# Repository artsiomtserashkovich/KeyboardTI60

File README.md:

TI60
===

A common 60% PCB with RGB Backlight.

## TI60 Hardware Information

    MCU: Atmega32u4
    Led Driver: IS31FL3731
    Leds: WS2812
    
    Led Pin: D2
    Led Drive Pins: D0 D1 (I2C) 

    /* Column pin configuration
    * col: 1   2   3   4   5   6   7   8   9   10   11  12  13  14  15
    * pin: F1  B0  F5  B1  F6  B2  F7  B3  C7  B7   C6  D3  B6  D5  F0
    */
     
    /* Row pin configuration
    * row: 1   2   3   4   5
    * pin: D4  D6  D7  B4  B5
    */

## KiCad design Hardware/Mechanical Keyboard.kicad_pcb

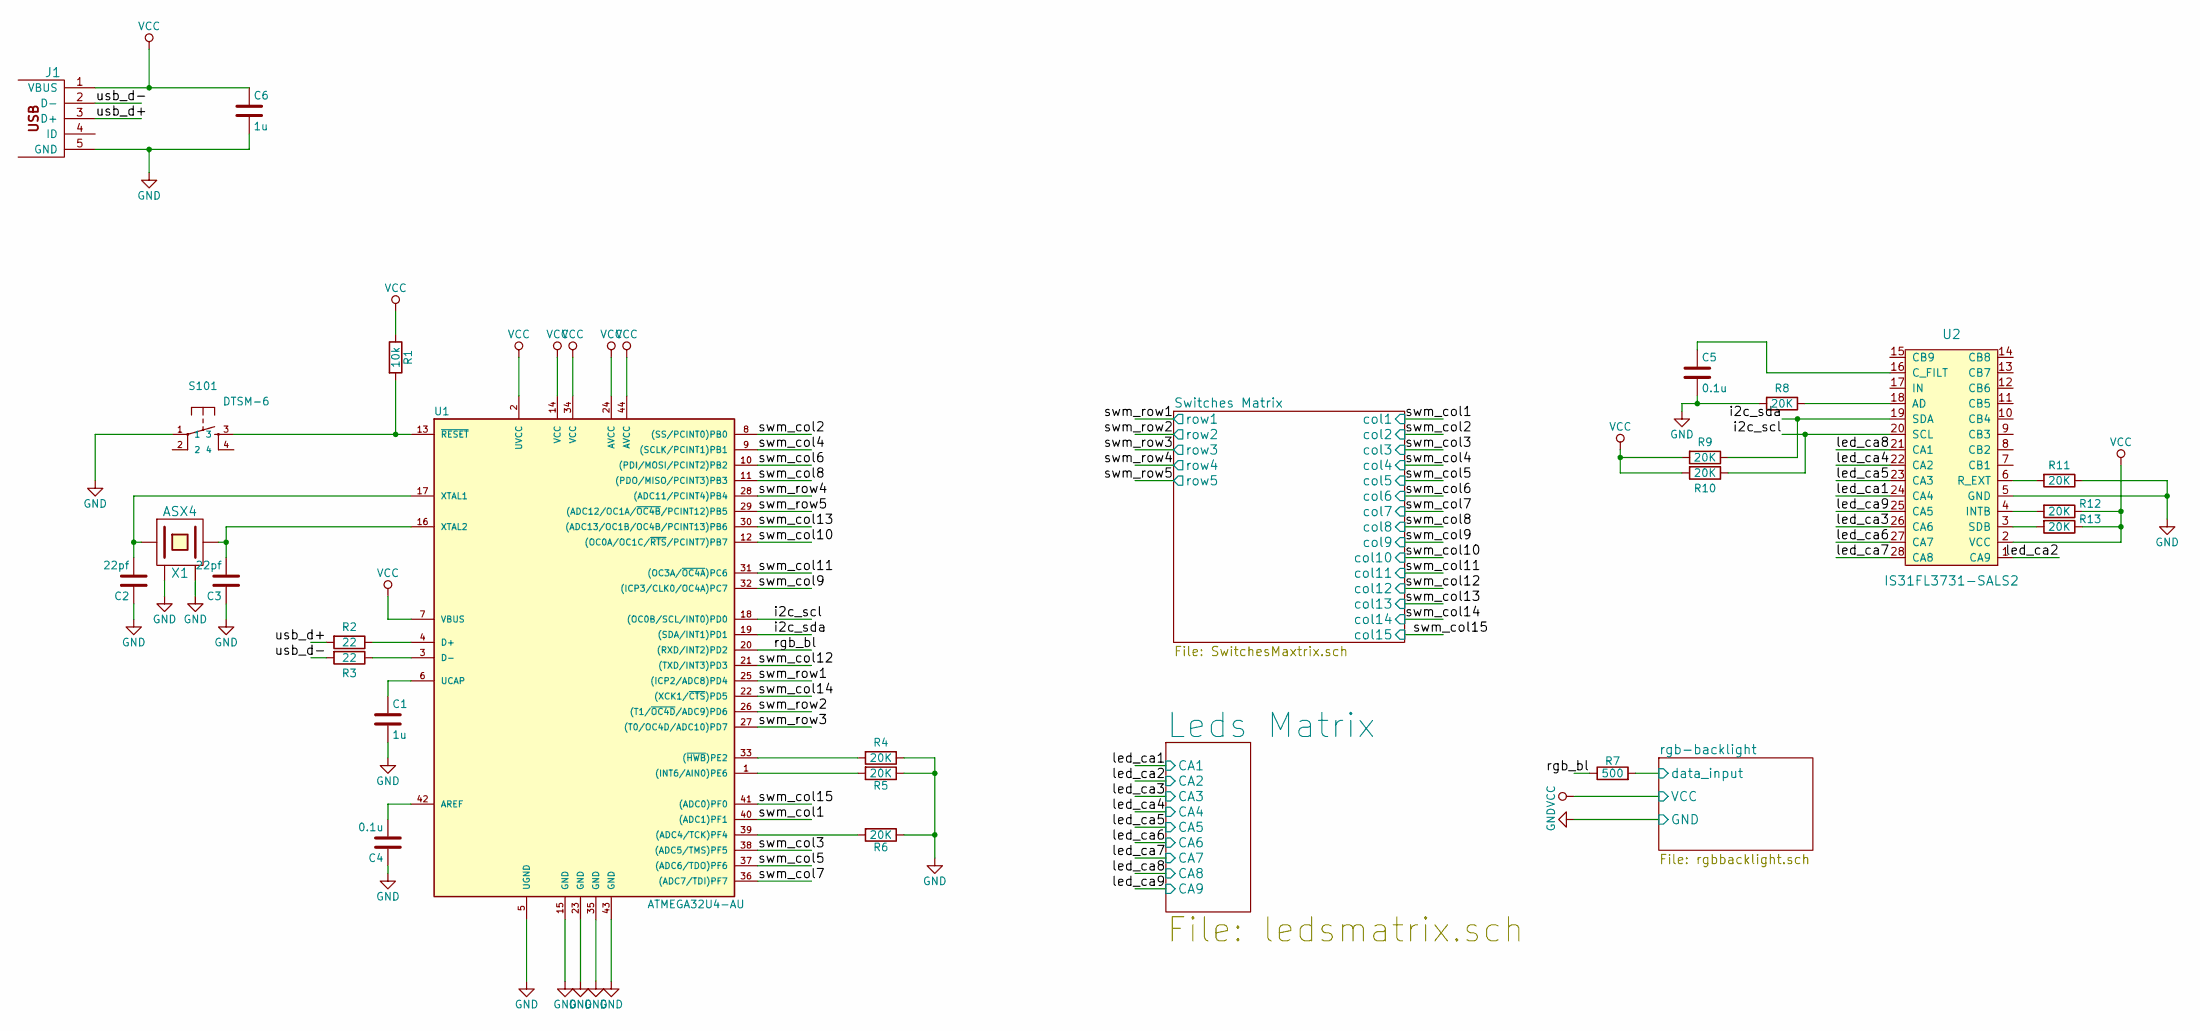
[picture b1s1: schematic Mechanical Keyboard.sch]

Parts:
C1, C6: 1u; C_0805_HandSoldering
C2, C3: 22pf; C_0805_HandSoldering
C4, C5: 0.1u; C_0805_HandSoldering
J1: USBMINI_B05; 67503
R1: 10k; R_0805_HandSoldering
R2, R3: 22; R_0805_HandSoldering
R4, R5, R6, R8, R9, R10, R11, R12, R13: 20K; R_0805_HandSoldering
R7: 500; R_0805_HandSoldering
S101: DTSM-6; KSEM31GLFS
U1: ATMEGA32U4-AU; TQFP-44_10x10mm_Pitch0.8mm
U2: IS31FL3731-SALS2; QFN-28-1EP_4x4mm_Pitch0.4mm
X1: ASX4; 4-SMD

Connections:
/i2c_scl: R10.1, U1.18 ((OC0B/SCL/INT0)PD0), U2.20 (SCL)
/i2c_sda: R9.1, U1.19 ((SDA/INT1)PD1), U2.19 (SDA)
/led_ca1: U2.24 (CA4); also elsewhere on the board
/led_ca2: U2.1 (CA9); also elsewhere on the board
/led_ca3: U2.26 (CA6); also elsewhere on the board
/led_ca4: U2.22 (CA2); also elsewhere on the board
/led_ca5: U2.23 (CA3); also elsewhere on the board
/led_ca6: U2.27 (CA7); also elsewhere on the board
/led_ca7: U2.28 (CA8); also elsewhere on the board
/led_ca8: U2.21 (CA1); also elsewhere on the board
/led_ca9: U2.25 (CA5); also elsewhere on the board
/rgb-backlight/data_input: R7.2; also elsewhere on the board
/rgb_bl: R7.1, U1.20 ((RXD/INT2)PD2)
/swm_col1: U1.40 ((ADC1)PF1); also elsewhere on the board
/swm_col2: U1.8 ((SS/PCINT0)PB0); also elsewhere on the board
/swm_col3: U1.38 ((ADC5/TMS)PF5); also elsewhere on the board
/swm_col4: U1.9 ((SCLK/PCINT1)PB1); also elsewhere on the board
/swm_col5: U1.37 ((ADC6/TDO)PF6); also elsewhere on the board
/swm_col6: U1.10 ((PDI/MOSI/PCINT2)PB2); also elsewhere on the board
/swm_col7: U1.36 ((ADC7/TDI)PF7); also elsewhere on the board
/swm_col8: U1.11 ((PDO/MISO/PCINT3)PB3); also elsewhere on the board
/swm_col9: U1.32 ((ICP3/CLK0/OC4A)PC7); also elsewhere on the board
/swm_col10: U1.12 ((OC0A/OC1C/~RTS~/PCINT7)PB7); also elsewhere on the board
/swm_col11: U1.31 ((OC3A/~OC4A~)PC6); also elsewhere on the board
/swm_col12: U1.21 ((TXD/INT3)PD3); also elsewhere on the board
/swm_col13: U1.30 ((ADC13/OC1B/OC4B/PCINT13)PB6); also elsewhere on the board
/swm_col14: U1.22 ((XCK1/~CTS~)PD5); also elsewhere on the board
/swm_col15: U1.41 ((ADC0)PF0); also elsewhere on the board
/swm_row1: U1.25 ((ICP2/ADC8)PD4); also elsewhere on the board
/swm_row2: U1.26 ((T1/~OC4D~/ADC9)PD6); also elsewhere on the board
/swm_row3: U1.27 ((T0/OC4D/ADC10)PD7); also elsewhere on the board
/swm_row4: U1.28 ((ADC11/PCINT4)PB4); also elsewhere on the board
/swm_row5: U1.29 ((ADC12/OC1A/~OC4B~/PCINT12)PB5); also elsewhere on the board
/usb_d+: J1.3 (D+), R2.2
/usb_d-: J1.2 (D-), R3.2
GND: C1.2, C2.1, C3.1, C4.1, C5.2, C6.2, J1.5 (GND), R4.1, R5.1, R6.1, R8.2, R11.1, S101.1, U1.5 (UGND), U1.15 (GND), U1.23 (GND), U1.35 (GND), U1.43 (GND), U2.5 (GND), X1.2 (GND), X1.4 (GND); also elsewhere on the board
unnamed: C1.1, U1.6 (UCAP)
unnamed: C2.2, U1.17 (XTAL1), X1.1
unnamed: C3.2, U1.16 (XTAL2), X1.3 (2)
unnamed: C4.2, U1.42 (AREF)
unnamed: C5.1, U2.16 (C_FILT)
unnamed: R1.2, S101.3, U1.13 (~RESET~)
unnamed: R2.1, U1.4 (D+)
unnamed: R3.1, U1.3 (D-)
unnamed: R4.2, U1.33 ((~HWB~)PE2)
unnamed: R5.2, U1.1 ((INT6/AIN0)PE6)
unnamed: R6.2, U1.39 ((ADC4/TCK)PF4)
unnamed: R8.1, U2.18 (AD)
unnamed: R11.2, U2.6 (R_EXT)
unnamed: R12.2, U2.4 (INTB)
unnamed: R13.2, U2.3 (SDB)
VCC: C6.1, J1.1 (VBUS), R1.1, R9.2, R10.2, R12.1, R13.1, U1.2 (UVCC), U1.7 (VBUS), U1.14 (VCC), U1.24 (AVCC), U1.34 (VCC), U1.44 (AVCC), U2.2 (VCC); also elsewhere on the board

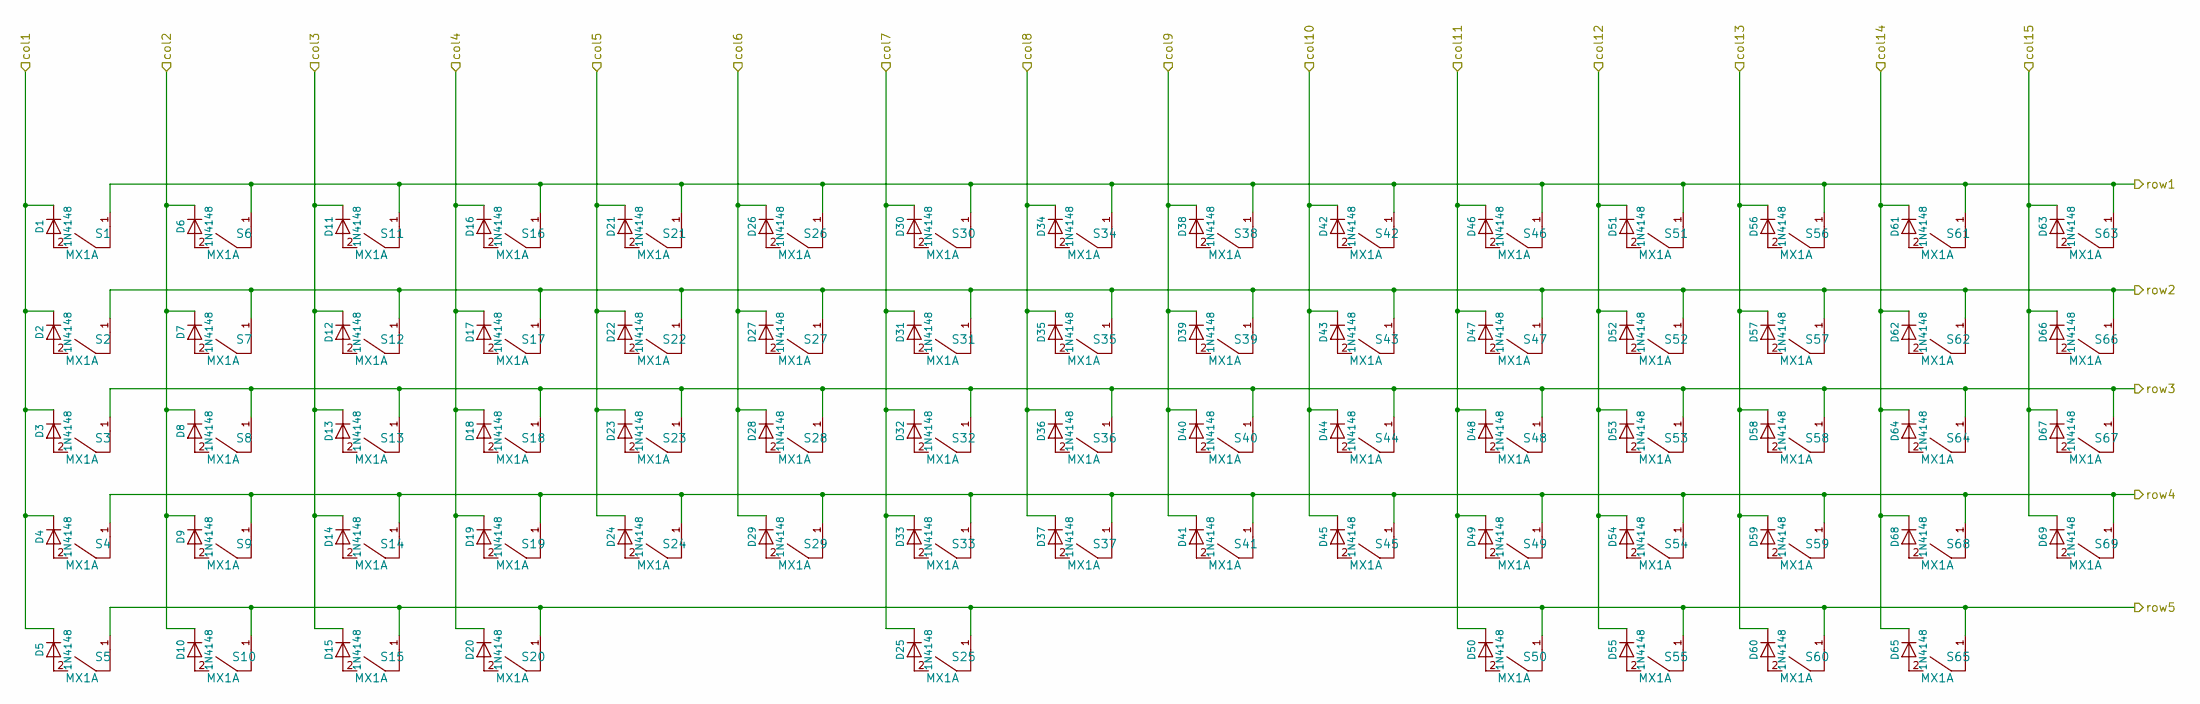
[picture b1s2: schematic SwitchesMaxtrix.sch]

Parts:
D1, D2, D3, D4, D5, D6, D7, D8, D9, D10, D11, D12, D13, D14, D15, D16, D17, D18, D19, D20, D21, D22, D23, D24, D25, D26, D27, D28, D29, D30, D31, D32, D33, D34, D35, D36, D37, D38, D39, D40, D41, D42, D43, D44, D45, D46, D47, D48, D49, D50, D51, D52, D53, D54, D55, D56, D57, D58, D59, D60, D61, D62, D63, D64, D65, D66, D67, D68, D69: 1N4148; D_SOD-123
S1, S2, S3, S4, S5, S6, S7, S8, S9, S10, S11, S12, S13, S14, S15, S16, S17, S18, S19, S20, S21, S22, S23, S24, S25, S26, S27, S28, S29, S30, S31, S32, S33, S34, S35, S36, S37, S38, S39, S40, S41, S42, S43, S44, S45, S46, S47, S48, S49, S50, S51, S52, S53, S54, S55, S56, S57, S58, S59, S60, S61, S62, S63, S64, S65, S66, S67, S68, S69: MX1A

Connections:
/swm_col1: D1.1 (K), D2.1 (K), D3.1 (K), D4.1 (K), D5.1 (K); also elsewhere on the board
/swm_col2: D6.1 (K), D7.1 (K), D8.1 (K), D9.1 (K), D10.1 (K); also elsewhere on the board
/swm_col3: D11.1 (K), D12.1 (K), D13.1 (K), D14.1 (K), D15.1 (K); also elsewhere on the board
/swm_col4: D16.1 (K), D17.1 (K), D18.1 (K), D19.1 (K), D20.1 (K); also elsewhere on the board
/swm_col5: D21.1 (K), D22.1 (K), D23.1 (K), D24.1 (K); also elsewhere on the board
/swm_col6: D26.1 (K), D27.1 (K), D28.1 (K), D29.1 (K); also elsewhere on the board
/swm_col7: D25.1 (K), D30.1 (K), D31.1 (K), D32.1 (K), D33.1 (K); also elsewhere on the board
/swm_col8: D34.1 (K), D35.1 (K), D36.1 (K), D37.1 (K); also elsewhere on the board
/swm_col9: D38.1 (K), D39.1 (K), D40.1 (K), D41.1 (K); also elsewhere on the board
/swm_col10: D42.1 (K), D43.1 (K), D44.1 (K), D45.1 (K); also elsewhere on the board
/swm_col11: D46.1 (K), D47.1 (K), D48.1 (K), D49.1 (K), D50.1 (K); also elsewhere on the board
/swm_col12: D51.1 (K), D52.1 (K), D53.1 (K), D54.1 (K), D55.1 (K); also elsewhere on the board
/swm_col13: D56.1 (K), D57.1 (K), D58.1 (K), D59.1 (K), D60.1 (K); also elsewhere on the board
/swm_col14: D61.1 (K), D62.1 (K), D64.1 (K), D65.1 (K), D68.1 (K); also elsewhere on the board
/swm_col15: D63.1 (K), D66.1 (K), D67.1 (K), D69.1 (K); also elsewhere on the board
/swm_row1: S1.1, S6.1, S11.1, S16.1, S21.1, S26.1, S30.1, S34.1, S38.1, S42.1, S46.1, S51.1, S56.1, S61.1, S63.1; also elsewhere on the board
/swm_row2: S2.1, S7.1, S12.1, S17.1, S22.1, S27.1, S31.1, S35.1, S39.1, S43.1, S47.1, S52.1, S57.1, S62.1, S66.1; also elsewhere on the board
/swm_row3: S3.1, S8.1, S13.1, S18.1, S23.1, S28.1, S32.1, S36.1, S40.1, S44.1, S48.1, S53.1, S58.1, S64.1, S67.1; also elsewhere on the board
/swm_row4: S4.1, S9.1, S14.1, S19.1, S24.1, S29.1, S33.1, S37.1, S41.1, S45.1, S49.1, S54.1, S59.1, S68.1, S69.1; also elsewhere on the board
/swm_row5: S5.1, S10.1, S15.1, S20.1, S25.1, S50.1, S55.1, S60.1, S65.1; also elsewhere on the board
unnamed: D1.2 (A), S1.2
unnamed: D2.2 (A), S2.2
unnamed: D3.2 (A), S3.2
unnamed: D4.2 (A), S4.2
unnamed: D5.2 (A), S5.2
unnamed: D6.2 (A), S6.2
unnamed: D7.2 (A), S7.2
unnamed: D8.2 (A), S8.2
unnamed: D9.2 (A), S9.2
unnamed: D10.2 (A), S10.2
unnamed: D11.2 (A), S11.2
unnamed: D12.2 (A), S12.2
unnamed: D13.2 (A), S13.2
unnamed: D14.2 (A), S14.2
unnamed: D15.2 (A), S15.2
unnamed: D16.2 (A), S16.2
unnamed: D17.2 (A), S17.2
unnamed: D18.2 (A), S18.2
unnamed: D19.2 (A), S19.2
unnamed: D20.2 (A), S20.2
unnamed: D21.2 (A), S21.2
unnamed: D22.2 (A), S22.2
unnamed: D23.2 (A), S23.2
unnamed: D24.2 (A), S24.2
unnamed: D25.2 (A), S25.2
unnamed: D26.2 (A), S26.2
unnamed: D27.2 (A), S27.2
unnamed: D28.2 (A), S28.2
unnamed: D29.2 (A), S29.2
unnamed: D30.2 (A), S30.2
unnamed: D31.2 (A), S31.2
unnamed: D32.2 (A), S32.2
unnamed: D33.2 (A), S33.2
unnamed: D34.2 (A), S34.2
unnamed: D35.2 (A), S35.2
unnamed: D36.2 (A), S36.2
unnamed: D37.2 (A), S37.2
unnamed: D38.2 (A), S38.2
unnamed: D39.2 (A), S39.2
unnamed: D40.2 (A), S40.2
unnamed: D41.2 (A), S41.2
unnamed: D42.2 (A), S42.2
unnamed: D43.2 (A), S43.2
unnamed: D44.2 (A), S44.2
unnamed: D45.2 (A), S45.2
unnamed: D46.2 (A), S46.2
unnamed: D47.2 (A), S47.2
unnamed: D48.2 (A), S48.2
unnamed: D49.2 (A), S49.2
unnamed: D50.2 (A), S50.2
unnamed: D51.2 (A), S51.2
unnamed: D52.2 (A), S52.2
unnamed: D53.2 (A), S53.2
unnamed: D54.2 (A), S54.2
unnamed: D55.2 (A), S55.2
unnamed: D56.2 (A), S56.2
unnamed: D57.2 (A), S57.2
unnamed: D58.2 (A), S58.2
unnamed: D59.2 (A), S59.2
unnamed: D60.2 (A), S60.2
unnamed: D61.2 (A), S61.2
unnamed: D62.2 (A), S62.2
unnamed: D63.2 (A), S63.2
unnamed: D64.2 (A), S64.2
unnamed: D65.2 (A), S65.2
unnamed: D66.2 (A), S66.2
unnamed: D67.2 (A), S67.2
unnamed: D68.2 (A), S68.2
unnamed: D69.2 (A), S69.2

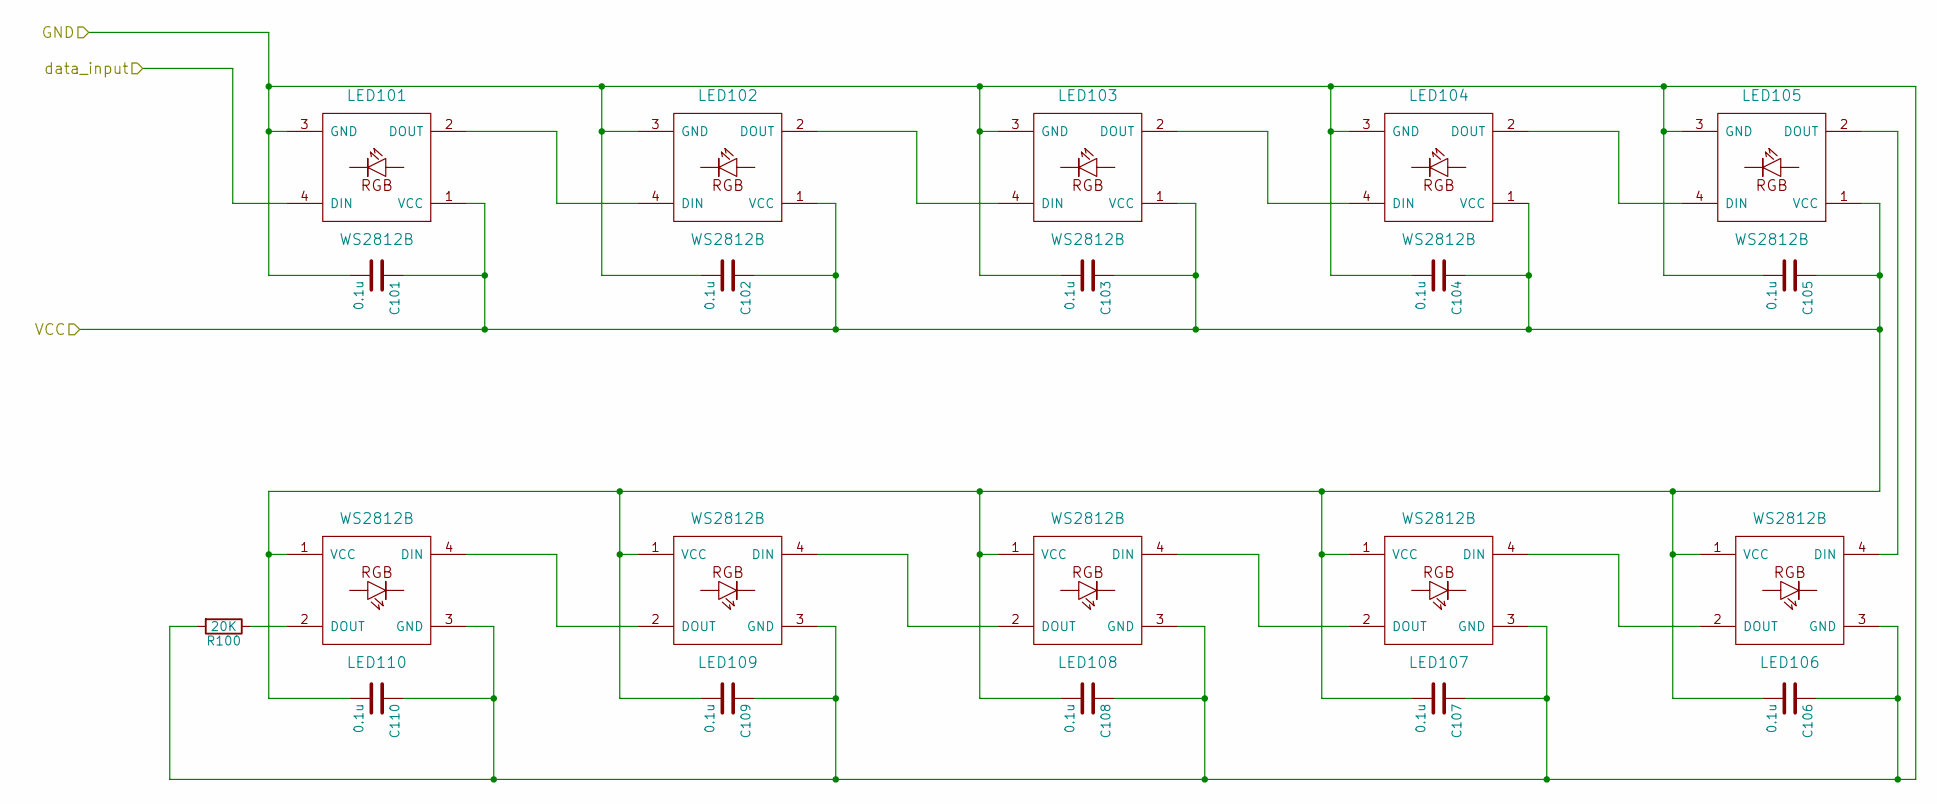
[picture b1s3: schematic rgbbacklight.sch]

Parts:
C101, C102, C103, C104, C105, C106, C107, C108, C109, C110: 0.1u; C_0805_HandSoldering
LED101, LED102, LED103, LED104, LED105, LED106, LED107, LED108, LED109, LED110: WS2812B
R100: 20K; R_0805_HandSoldering

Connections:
/rgb-backlight/data_input: LED101.4 (DIN); also elsewhere on the board
GND: C101.2, C102.2, C103.2, C104.2, C105.2, C106.1, C107.1, C108.1, C109.1, C110.1, LED101.3 (GND), LED102.3 (GND), LED103.3 (GND), LED104.3 (GND), LED105.3 (GND), LED106.3 (GND), LED107.3 (GND), LED108.3 (GND), LED109.3 (GND), LED110.3 (GND), R100.2; also elsewhere on the board
unnamed: LED101.2 (DOUT), LED102.4 (DIN)
unnamed: LED102.2 (DOUT), LED103.4 (DIN)
unnamed: LED103.2 (DOUT), LED104.4 (DIN)
unnamed: LED104.2 (DOUT), LED105.4 (DIN)
unnamed: LED105.2 (DOUT), LED106.4 (DIN)
unnamed: LED106.2 (DOUT), LED107.4 (DIN)
unnamed: LED107.2 (DOUT), LED108.4 (DIN)
unnamed: LED108.2 (DOUT), LED109.4 (DIN)
unnamed: LED109.2 (DOUT), LED110.4 (DIN)
unnamed: LED110.2 (DOUT), R100.1
VCC: C101.1, C102.1, C103.1, C104.1, C105.1, C106.2, C107.2, C108.2, C109.2, C110.2, LED101.1 (VCC), LED102.1 (VCC), LED103.1 (VCC), LED104.1 (VCC), LED105.1 (VCC), LED106.1 (VCC), LED107.1 (VCC), LED108.1 (VCC), LED109.1 (VCC), LED110.1 (VCC); also elsewhere on the board

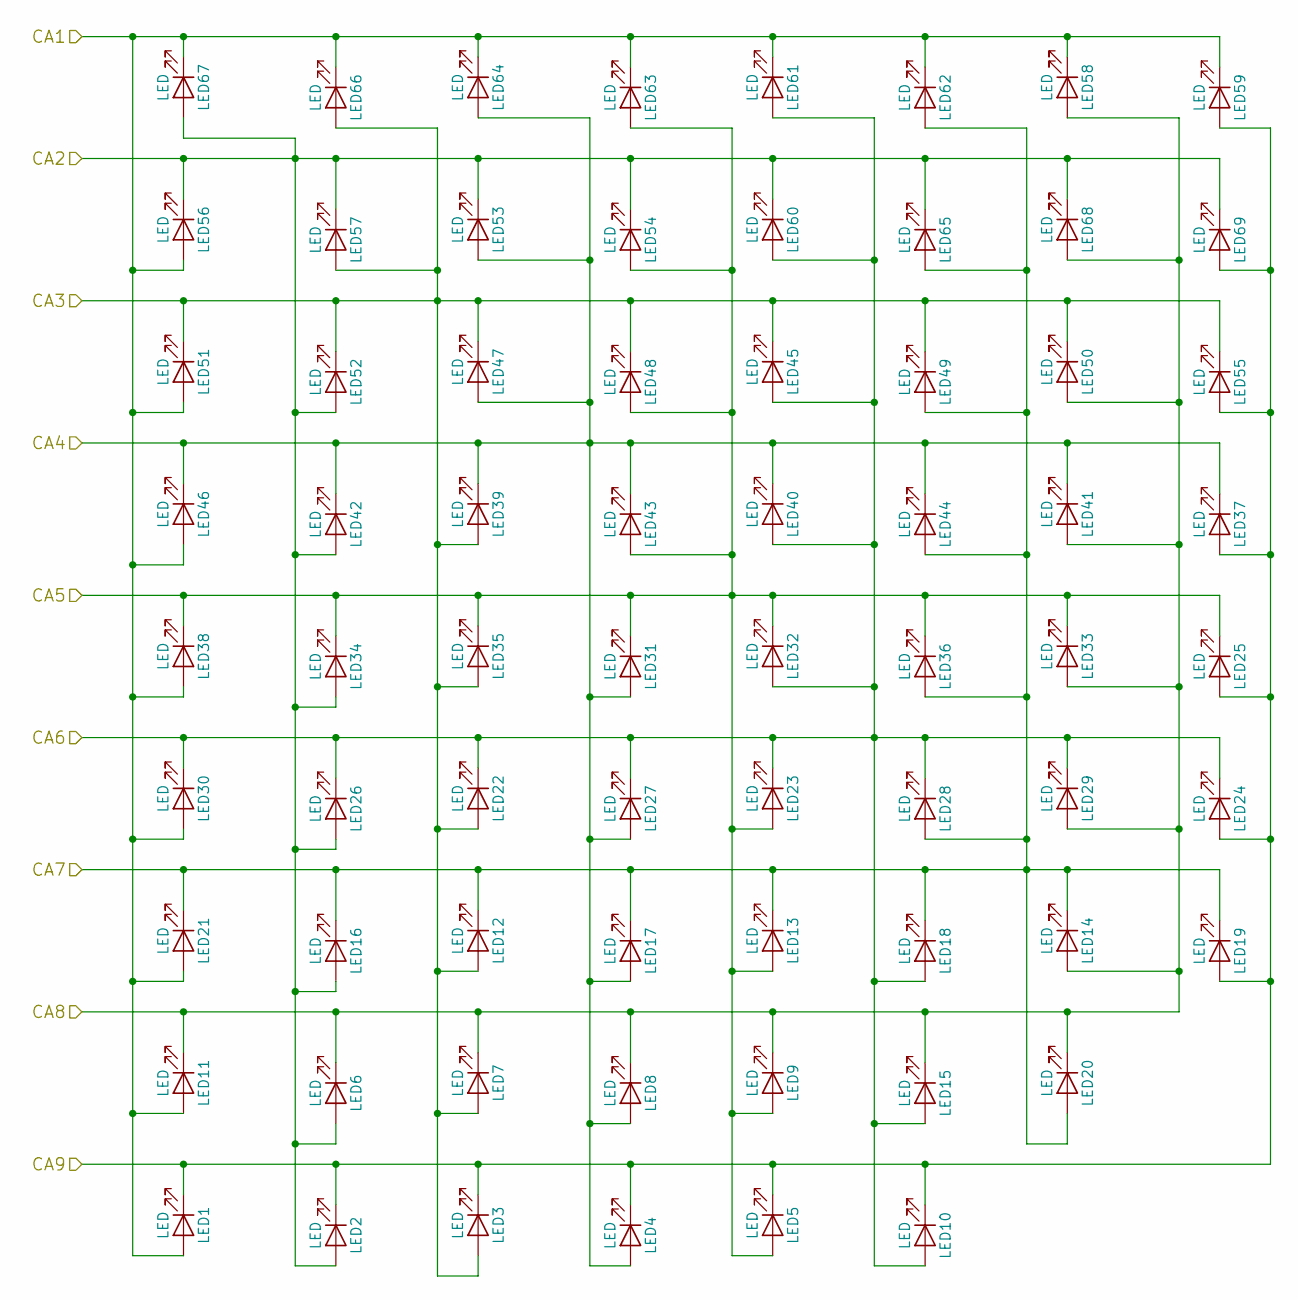
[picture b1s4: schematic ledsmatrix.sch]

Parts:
LED1, LED2, LED3, LED4, LED5, LED6, LED7, LED8, LED9, LED10, LED11, LED12, LED13, LED14, LED15, LED16, LED17, LED18, LED19, LED20, LED21, LED22, LED23, LED24, LED25, LED26, LED27, LED28, LED29, LED30, LED31, LED32, LED33, LED34, LED35, LED36, LED37, LED38, LED39, LED40, LED41, LED42, LED43, LED44, LED45, LED46, LED47, LED48, LED49, LED50, LED51, LED52, LED53, LED54, LED55, LED56, LED57, LED58, LED59, LED60, LED61, LED62, LED63, LED64, LED65, LED66, LED67, LED68, LED69: LED; MX1A-led

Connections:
/led_ca1: LED1.2 (A), LED11.2 (A), LED21.2 (A), LED30.2 (A), LED38.2 (A), LED46.2 (A), LED51.2 (A), LED56.2 (A), LED58.1 (K), LED59.1 (K), LED61.1 (K), LED62.1 (K), LED63.1 (K), LED64.1 (K), LED66.1 (K), LED67.1 (K); also elsewhere on the board
/led_ca2: LED2.2 (A), LED6.2 (A), LED16.2 (A), LED26.2 (A), LED34.2 (A), LED42.2 (A), LED52.2 (A), LED53.1 (K), LED54.1 (K), LED56.1 (K), LED57.1 (K), LED60.1 (K), LED65.1 (K), LED67.2 (A), LED68.1 (K), LED69.1 (K); also elsewhere on the board
/led_ca3: LED3.2 (A), LED7.2 (A), LED12.2 (A), LED22.2 (A), LED35.2 (A), LED39.2 (A), LED45.1 (K), LED47.1 (K), LED48.1 (K), LED49.1 (K), LED50.1 (K), LED51.1 (K), LED52.1 (K), LED55.1 (K), LED57.2 (A), LED66.2 (A); also elsewhere on the board
/led_ca4: LED4.2 (A), LED8.2 (A), LED17.2 (A), LED27.2 (A), LED31.2 (A), LED37.1 (K), LED39.1 (K), LED40.1 (K), LED41.1 (K), LED42.1 (K), LED43.1 (K), LED44.1 (K), LED46.1 (K), LED47.2 (A), LED53.2 (A), LED64.2 (A); also elsewhere on the board
/led_ca5: LED5.2 (A), LED9.2 (A), LED13.2 (A), LED23.2 (A), LED25.1 (K), LED31.1 (K), LED32.1 (K), LED33.1 (K), LED34.1 (K), LED35.1 (K), LED36.1 (K), LED38.1 (K), LED43.2 (A), LED48.2 (A), LED54.2 (A), LED63.2 (A); also elsewhere on the board
/led_ca6: LED10.2 (A), LED15.2 (A), LED18.2 (A), LED22.1 (K), LED23.1 (K), LED24.1 (K), LED26.1 (K), LED27.1 (K), LED28.1 (K), LED29.1 (K), LED30.1 (K), LED32.2 (A), LED40.2 (A), LED45.2 (A), LED60.2 (A), LED61.2 (A); also elsewhere on the board
/led_ca7: LED12.1 (K), LED13.1 (K), LED14.1 (K), LED16.1 (K), LED17.1 (K), LED18.1 (K), LED19.1 (K), LED20.2 (A), LED21.1 (K), LED28.2 (A), LED36.2 (A), LED44.2 (A), LED49.2 (A), LED62.2 (A), LED65.2 (A); also elsewhere on the board
/led_ca8: LED6.1 (K), LED7.1 (K), LED8.1 (K), LED9.1 (K), LED11.1 (K), LED14.2 (A), LED15.1 (K), LED20.1 (K), LED29.2 (A), LED33.2 (A), LED41.2 (A), LED50.2 (A), LED58.2 (A), LED68.2 (A); also elsewhere on the board
/led_ca9: LED1.1 (K), LED2.1 (K), LED3.1 (K), LED4.1 (K), LED5.1 (K), LED10.1 (K), LED19.2 (A), LED24.2 (A), LED25.2 (A), LED37.2 (A), LED55.2 (A), LED59.2 (A), LED69.2 (A); also elsewhere on the board

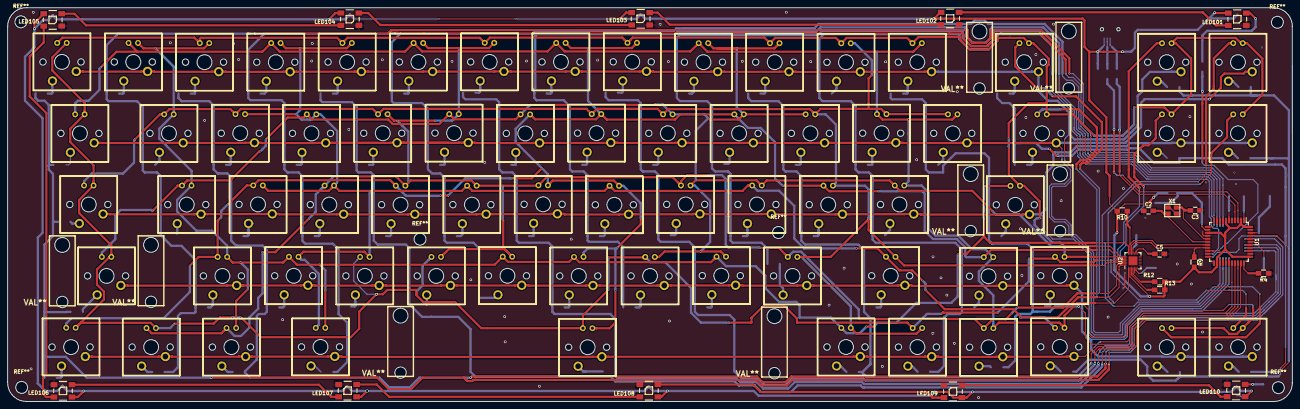
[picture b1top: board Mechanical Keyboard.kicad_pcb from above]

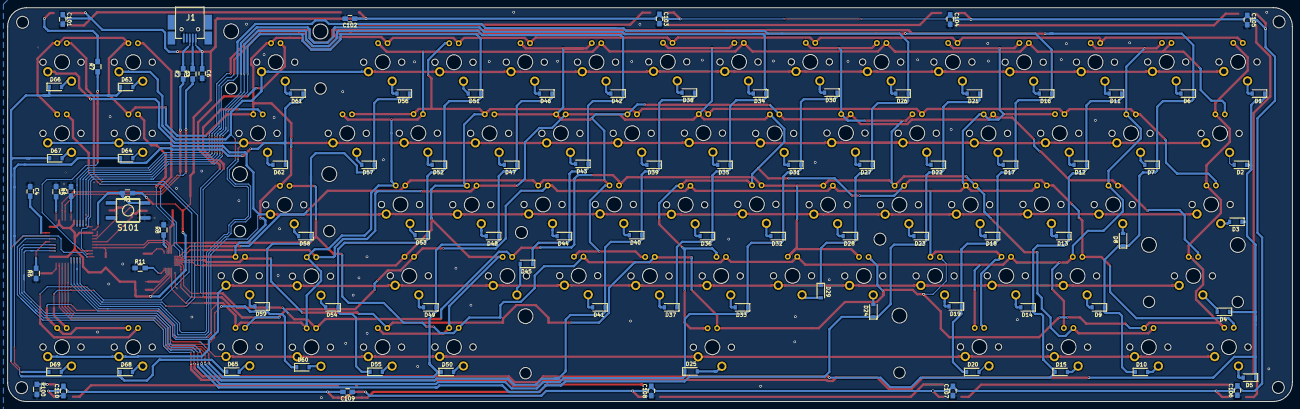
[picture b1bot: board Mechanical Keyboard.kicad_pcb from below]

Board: 2 copper layers, 343.4 x 105.3 mm, 260 parts (93 on the bottom side), 131 nets.

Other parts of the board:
MXST: VAL**; MXST
MXST#2, MXST#3, MXST#4, MXST#5, MXST#6, MXST#7, MXST#8: VAL**; MXST

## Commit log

2019-02-24 Initial
2019-02-24 refactorpcb
2019-03-03 Move diodes and resistors
2019-03-03 Add BOM list and add cut area
2019-03-03 Implement wiring
2019-03-04 wiring keys
2019-03-07 refactor wiring
2019-03-09 refactor
2019-03-25 Keyboard tracking was finished. Only GND circuit is left
2019-03-25 Small refactoring
2019-03-25 Bugfix for swm_col11 connection to atmega
2019-03-25 Temporary solution with GND filling
2019-03-25 GND curcuit fill was finished
2019-03-25 Bugfix for swm_col9
2019-03-25 add driling holes
2019-03-26 Atmega 5 GND pin refactoring
2019-05-08 clean up project
